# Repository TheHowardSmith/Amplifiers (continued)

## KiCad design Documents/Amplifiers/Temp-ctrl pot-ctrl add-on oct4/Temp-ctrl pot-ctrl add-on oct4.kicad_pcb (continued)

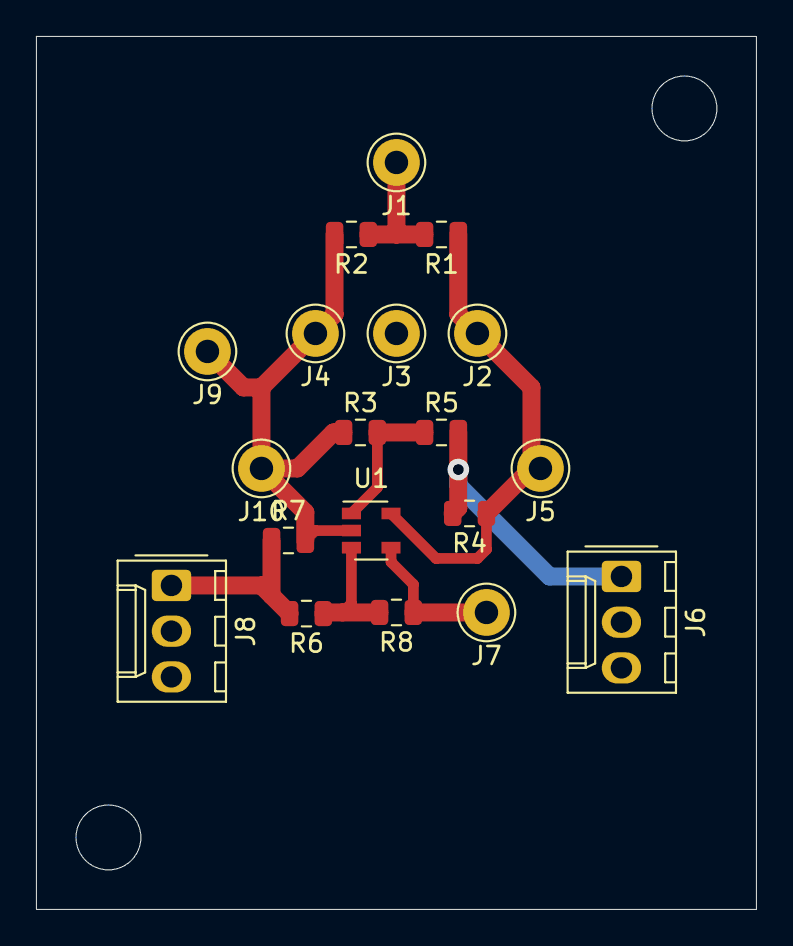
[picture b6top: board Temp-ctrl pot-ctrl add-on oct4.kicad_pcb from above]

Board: 2 copper layers, 40.0 x 48.5 mm, 19 parts (0 on the bottom side), 8 nets.

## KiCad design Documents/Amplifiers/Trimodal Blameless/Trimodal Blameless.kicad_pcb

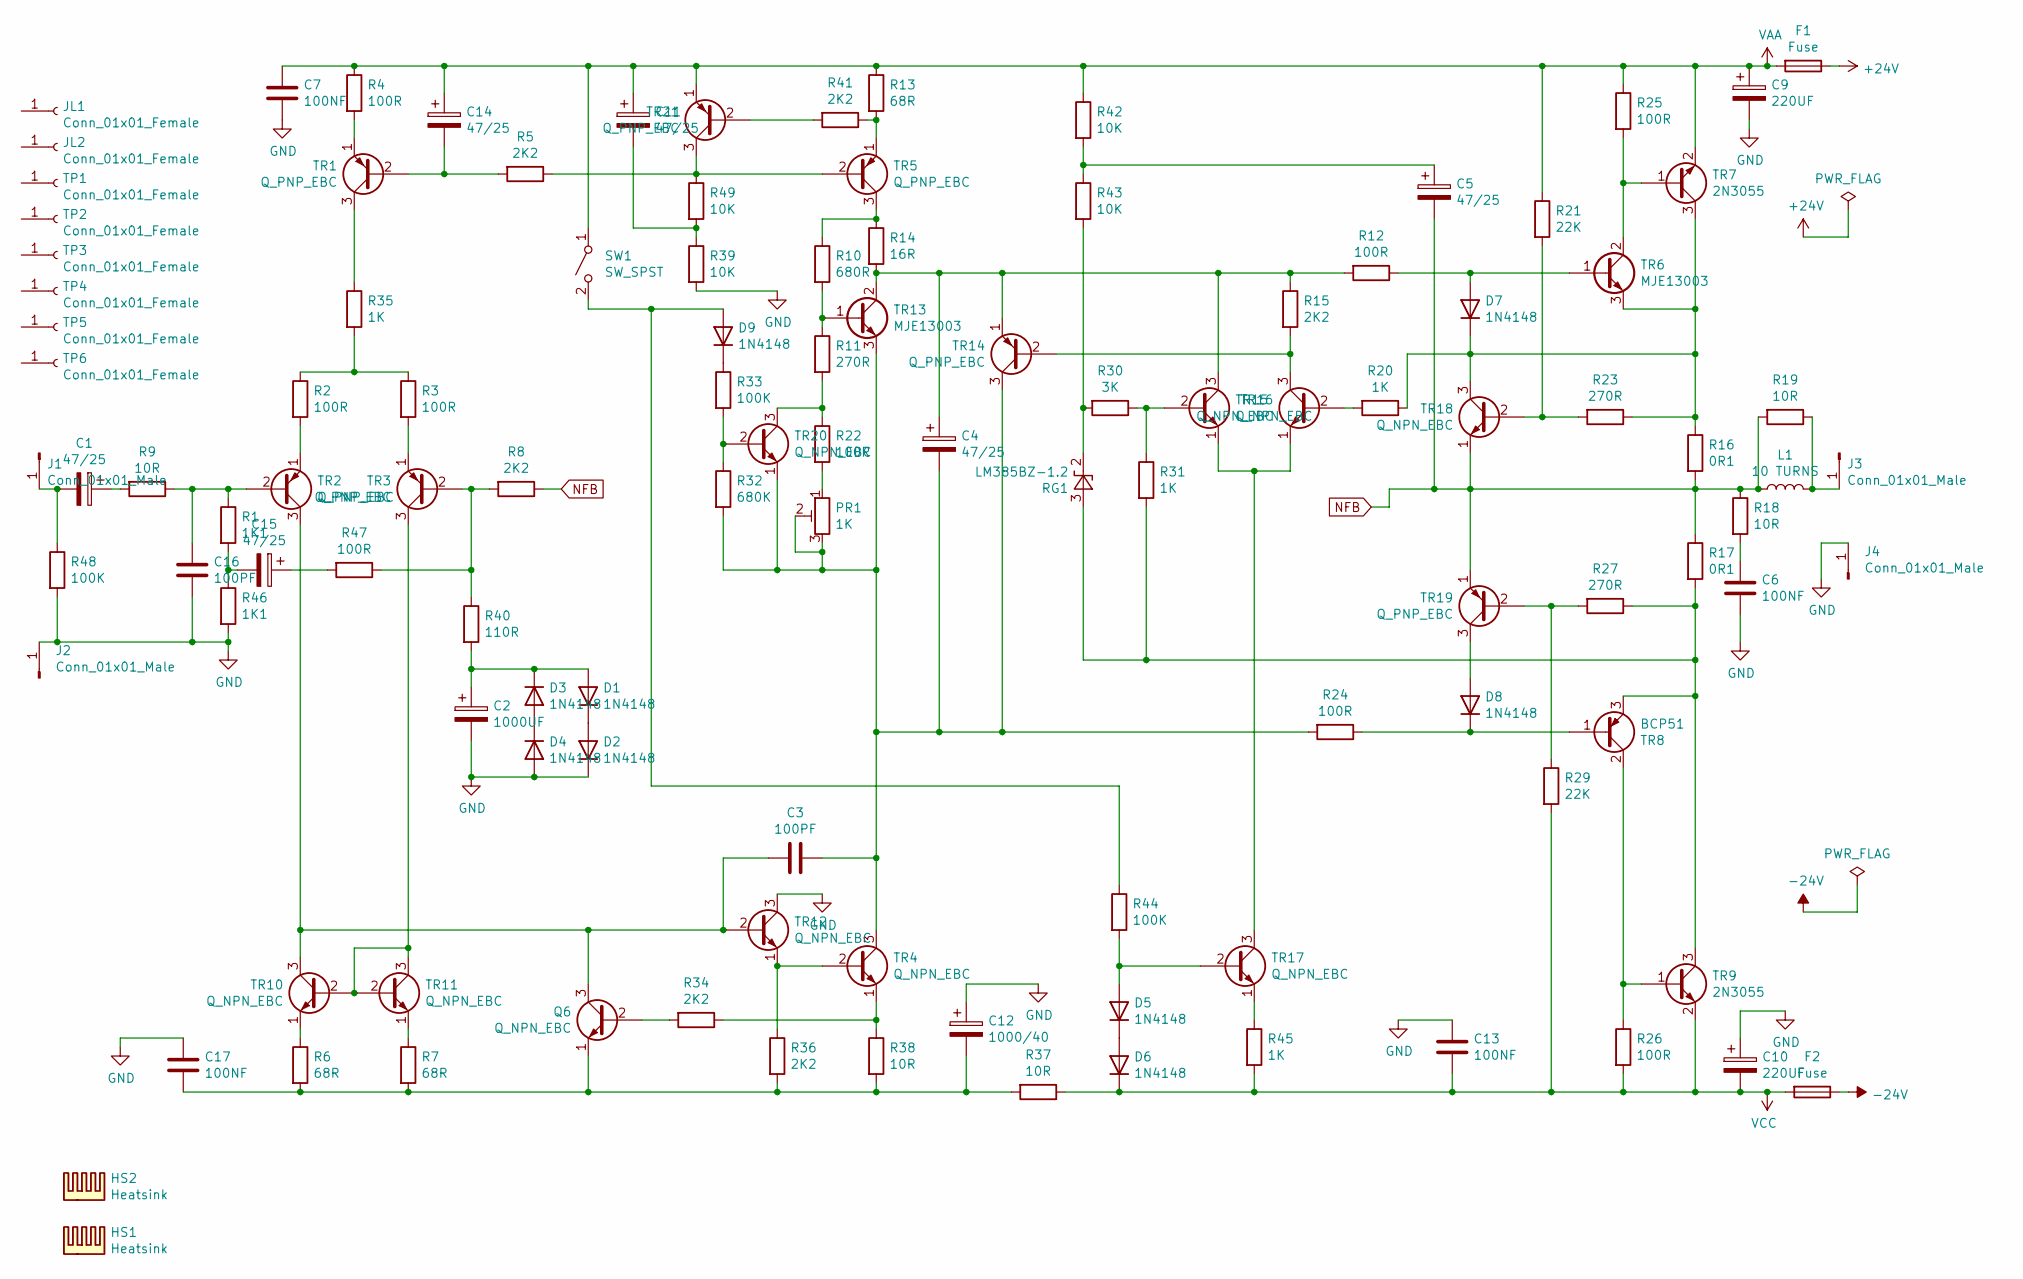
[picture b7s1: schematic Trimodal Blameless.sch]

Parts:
C1, C4, C5, C11, C14, C15: 47/25; CP_Radial_D8.0mm_P5.00mm
C2: 1000UF; CP_Radial_D10.0mm_P5.00mm
C3, C16: 100PF; C_Disc_D4.3mm_W1.9mm_P5.00mm
C6, C7, C13, C17: 100NF; C_Rect_L11.0mm_W3.5mm_P10.00mm_MKT
C9, C10: 220UF; CP_Radial_D10.0mm_P5.00mm
C12: 1000/40; CP_Radial_D12.5mm_P5.00mm
D1, D2, D3, D4, D5, D6, D7, D8, D9: 1N4148; D_DO-41_SOD81_P7.62mm_Horizontal
F1, F2: Fuse; Fuseholder_Cylinder-5x20mm_Stelvio-Kontek_PTF78_Horizontal_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
HS1, HS2: Heatsink; Heatsink_Fischer_SK104-STCB_35x13mm__2xDrill3.5mm_ScrewM3
J1, J2, J3, J4: Conn_01x01_Male; Pin_D1.3mm_L11.0mm
JL1, JL2: Conn_01x01_Female; Pin_D1.3mm_L11.0mm
L1: 10 TURNS; L_Axial_L20.3mm_D12.7mm_P25.40mm_Horizontal_Vishay_IHA-201
PR1: 1K; Potentiometer_ACP_CA9-V10_Vertical
Q6: Q_NPN_EBC; TO-92
R1, R46: 1K1; R_Axial_DIN0207_L6.3mm_D2.5mm_P10.16mm_Horizontal
R2, R3, R4, R12, R22, R24, R25, R26, R47: 100R; R_Axial_DIN0207_L6.3mm_D2.5mm_P10.16mm_Horizontal
R5, R8, R15, R34, R36, R41: 2K2; R_Axial_DIN0207_L6.3mm_D2.5mm_P10.16mm_Horizontal
R6, R7, R13: 68R; R_Axial_DIN0207_L6.3mm_D2.5mm_P10.16mm_Horizontal
R9, R18, R19, R37, R38: 10R; R_Axial_DIN0207_L6.3mm_D2.5mm_P10.16mm_Horizontal
R10: 680R; R_Axial_DIN0207_L6.3mm_D2.5mm_P10.16mm_Horizontal
R11, R23, R27: 270R; R_Axial_DIN0207_L6.3mm_D2.5mm_P10.16mm_Horizontal
R14: 16R; R_Axial_DIN0207_L6.3mm_D2.5mm_P10.16mm_Horizontal
R16, R17: 0R1; R_Axial_DIN0922_L20.0mm_D9.0mm_P30.48mm_Horizontal
R20, R31, R35, R45: 1K; R_Axial_DIN0207_L6.3mm_D2.5mm_P10.16mm_Horizontal
R21, R29: 22K; R_Axial_DIN0207_L6.3mm_D2.5mm_P10.16mm_Horizontal
R30: 3K; R_Axial_DIN0207_L6.3mm_D2.5mm_P10.16mm_Horizontal
R32: 680K; R_Axial_DIN0207_L6.3mm_D2.5mm_P10.16mm_Horizontal
R33, R44, R48: 100K; R_Axial_DIN0207_L6.3mm_D2.5mm_P10.16mm_Horizontal
R39, R42, R43, R49: 10K; R_Axial_DIN0207_L6.3mm_D2.5mm_P10.16mm_Horizontal
R40: 110R; R_Axial_DIN0207_L6.3mm_D2.5mm_P10.16mm_Horizontal
RG1: LM385BZ-1.2; TO-92_Inline
SW1: SW_SPST; SW_NKK_G1xJP
TP1, TP2, TP3, TP4, TP5, TP6: Conn_01x01_Female; Pin_D1.3mm_L11.0mm
TR1, TR2, TR3, TR5, TR14, TR19, TR21: Q_PNP_EBC; TO-92
TR4, TR10, TR11, TR12, TR15, TR16, TR17, TR18, TR20: Q_NPN_EBC; TO-92
TR6, TR13: MJE13003; TO-126-3_Vertical
TR7, TR9: 2N3055; TO-3
TR8: BCP51; TO-126-3_Vertical

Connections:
+24V: F1.1
-24V: F2.1
GND: C2.2, C6.2, C7.2, C9.2, C10.1, C12.1, C13.1, C16.2, C17.1, D2.1 (K), D4.2 (A), J2.1, J4.1, R39.2, R46.2, R48.2, TR12.3 (C)
NFB: C5.2, L1.1, R8.1, R16.2, R17.1, R18.1, R19.2, TR18.1 (E), TR19.1 (E)
unnamed: C1.1, R9.2
unnamed: C1.2, J1.1, R48.1
unnamed: C2.1, D1.2 (A), D3.1 (K), R40.2
unnamed: C3.1, C4.2, PR1.2, PR1.3, R24.2, R32.2, TR4.3 (C), TR13.3 (E), TR14.3 (C), TR20.1 (E)
unnamed: C3.2, Q6.3 (C), TR2.3 (C), TR10.3 (C), TR12.2 (B)
unnamed: C4.1, R12.2, R14.2, R15.1, TR13.2 (C), TR14.1 (E), TR15.3 (C)
unnamed: C5.1, R42.2, R43.1
unnamed: C6.1, R18.2
unnamed: C11.2, R39.1, R49.2
unnamed: C12.2, C17.2, Q6.1 (E), R6.2, R7.2, R36.2, R37.2, R38.2
unnamed: C14.2, R5.2, TR1.2 (B)
unnamed: C15.1, R47.2
unnamed: C15.2, R1.2, R46.1
unnamed: C16.1, R1.1, R9.1, TR2.2 (B)
unnamed: D1.1 (K), D2.2 (A)
unnamed: D3.2 (A), D4.1 (K)
unnamed: D5.1 (K), D6.2 (A)
unnamed: D5.2 (A), R44.2, TR17.2 (B)
unnamed: D7.1 (K), R16.1, R20.1, R23.1, TR6.3 (E), TR7.3 (C), TR18.3 (C)
unnamed: D7.2 (A), R12.1, TR6.1 (B)
unnamed: D8.1 (K), R24.1, TR8.1 (B)
unnamed: D8.2 (A), TR19.3 (C)
unnamed: D9.1 (K), R33.1
unnamed: D9.2 (A), R44.1, SW1.2 (B)
unnamed: J3.1, L1.2, R19.1
unnamed: PR1.1, R22.2
unnamed: Q6.2 (B), R34.2
unnamed: R2.1, R3.1, R35.2
unnamed: R2.2, TR2.1 (E)
unnamed: R3.2, TR3.1 (E)
unnamed: R4.2, TR1.1 (E)
unnamed: R6.1, TR10.1 (E)
unnamed: R7.1, TR11.1 (E)
unnamed: R10.1, R14.1, TR5.3 (C)
unnamed: R10.2, R11.1, TR13.1 (B)
unnamed: R11.2, R22.1, TR20.3 (C)
unnamed: R13.2, R41.1, TR5.1 (E)
unnamed: R15.2, TR14.2 (B), TR16.3 (C)
unnamed: R20.2, TR16.2 (B)
unnamed: R21.2, R23.2, TR18.2 (B)
unnamed: R25.2, TR6.2 (C), TR7.1 (B)
unnamed: R27.2, R29.1, TR19.2 (B)
unnamed: R30.1, R31.1, TR15.2 (B)
unnamed: R30.2, R43.2, RG1.2 (K)
unnamed: R32.1, R33.2, TR20.2 (B)
unnamed: R34.1, R38.1, TR4.1 (E)
unnamed: R35.1, TR1.3 (C)
unnamed: R36.1, TR4.2 (B), TR12.1 (E)
unnamed: R8.2, R40.1, R47.1, TR3.2 (B)
unnamed: R41.2, TR21.2 (B)
unnamed: R45.1, TR17.1 (E)
unnamed: R5.1, R49.1, TR5.2 (B), TR21.3 (C)
unnamed: TR3.3 (C), TR10.2 (B), TR11.2 (B), TR11.3 (C)
unnamed: TR15.1 (E), TR16.1 (E), TR17.3 (C)
VAA: C7.1, C9.1, C11.1, C14.1, F1.2, R4.1, R13.1, R21.1, R25.1, R42.1, SW1.1 (A), TR7.2 (E), TR21.1 (E)
VCC: C10.2, C13.2, D6.1 (K), F2.2, R26.2, R29.2, R37.1, R45.2, TR9.2 (E)

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
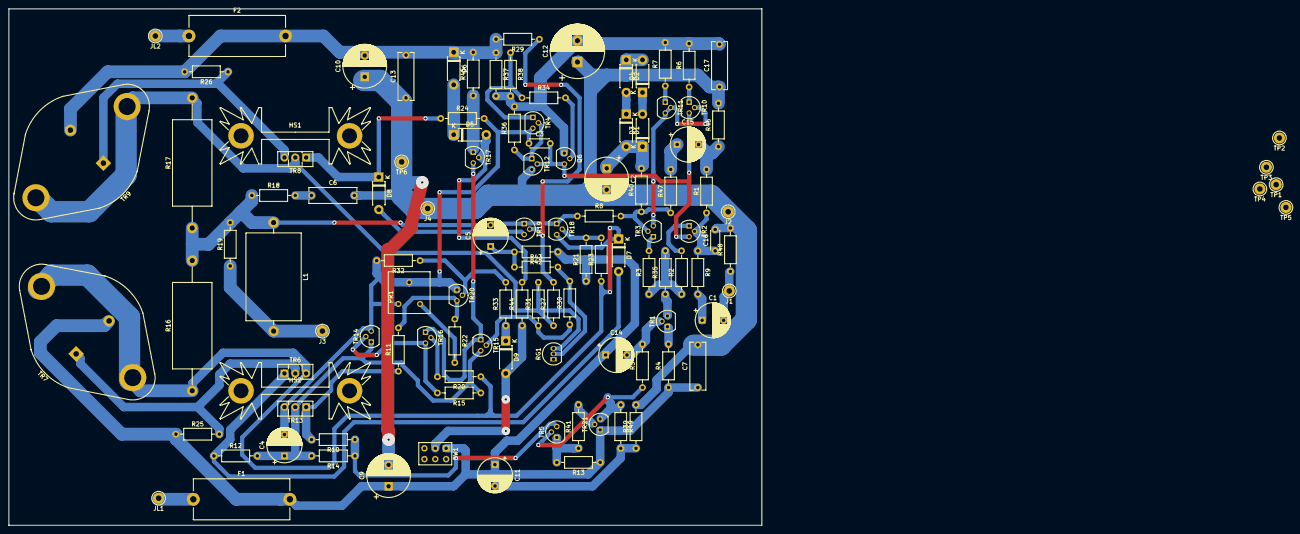
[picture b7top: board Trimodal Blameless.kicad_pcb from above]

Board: 2 copper layers, 176.3 x 120.9 mm, 115 parts (0 on the bottom side), 60 nets.

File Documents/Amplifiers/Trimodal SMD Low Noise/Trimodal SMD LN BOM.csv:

Comment,Designator,Footprint,LCSC
220UF,"C10,C9",Capacitor_SMD:CP_Elec_10x10,C176670
47/25,"C14,C1,C15,C11,C4,C5",Capacitor_SMD:CP_Elec_6.3x5.3,C249976
100PF,"C16,C3",Capacitor_SMD:C_0805_2012Metric,C1790
100NF,"C7,C17,C6,C13",Capacitor_SMD:C_0805_2012Metric,C49678
1N4148,"D3,D4,D1,D2,D9,D6,D5,D7,D8",Diode_SMD:D_SOD-123,C81598
1K1,"R1,R46",Resistor_SMD:R_0805_2012Metric,
680R,R10,Resistor_SMD:R_0805_2012Metric,
270R,"R11,R23,R27",Resistor_SMD:R_0805_2012Metric,
16R,R14,Resistor_SMD:R_0805_2012Metric,
0R1,"R16,R17,R166,R177",Resistor_SMD:R_2512_6332Metric,C78195
22K,"R21,R29",Resistor_SMD:R_0805_2012Metric,
3K,R30,Resistor_SMD:R_0805_2012Metric,
680K,R32,Resistor_SMD:R_0805_2012Metric,
1K,"R35,R45,R31,R20",Resistor_SMD:R_0805_2012Metric,
100R,"R4,R2,R3,R47,R24,R12,R25,R26,R22",Resistor_SMD:R_0805_2012Metric,
110R,R40,Resistor_SMD:R_0805_2012Metric,
100K,"R48,R33,R44",Resistor_SMD:R_0805_2012Metric,
10K,"R49,R39,R42,R43",Resistor_SMD:R_0805_2012Metric,
2K2,"R5,R8,R41,R36,R34,R15",Resistor_SMD:R_0805_2012Metric,
68R,"R6,R7,R13",Resistor_SMD:R_0805_2012Metric,
10R,"R9,R38,R37,R18,R19",Resistor_SMD:R_0805_2012Metric,
LM385M3X-2.5,RG1,Package_TO_SOT_SMD:SOT-23,C83345
SW_SPST,SW1,Package_SO:SOP-4_3.8x4.1mm_P2.54mm,C459807
Q_PNP_EBC,"TR1,TR3,TR2,TR21,TR5,TR14,TR19",Package_TO_SOT_SMD:SOT-89-3,C24278
Q_NPN_EBC,"TR10,TR11,TR20,TR4,TR12,Q6,TR15,TR16,TR18,TR17",Package_TO_SOT_SMD:SOT-89-3,C9634

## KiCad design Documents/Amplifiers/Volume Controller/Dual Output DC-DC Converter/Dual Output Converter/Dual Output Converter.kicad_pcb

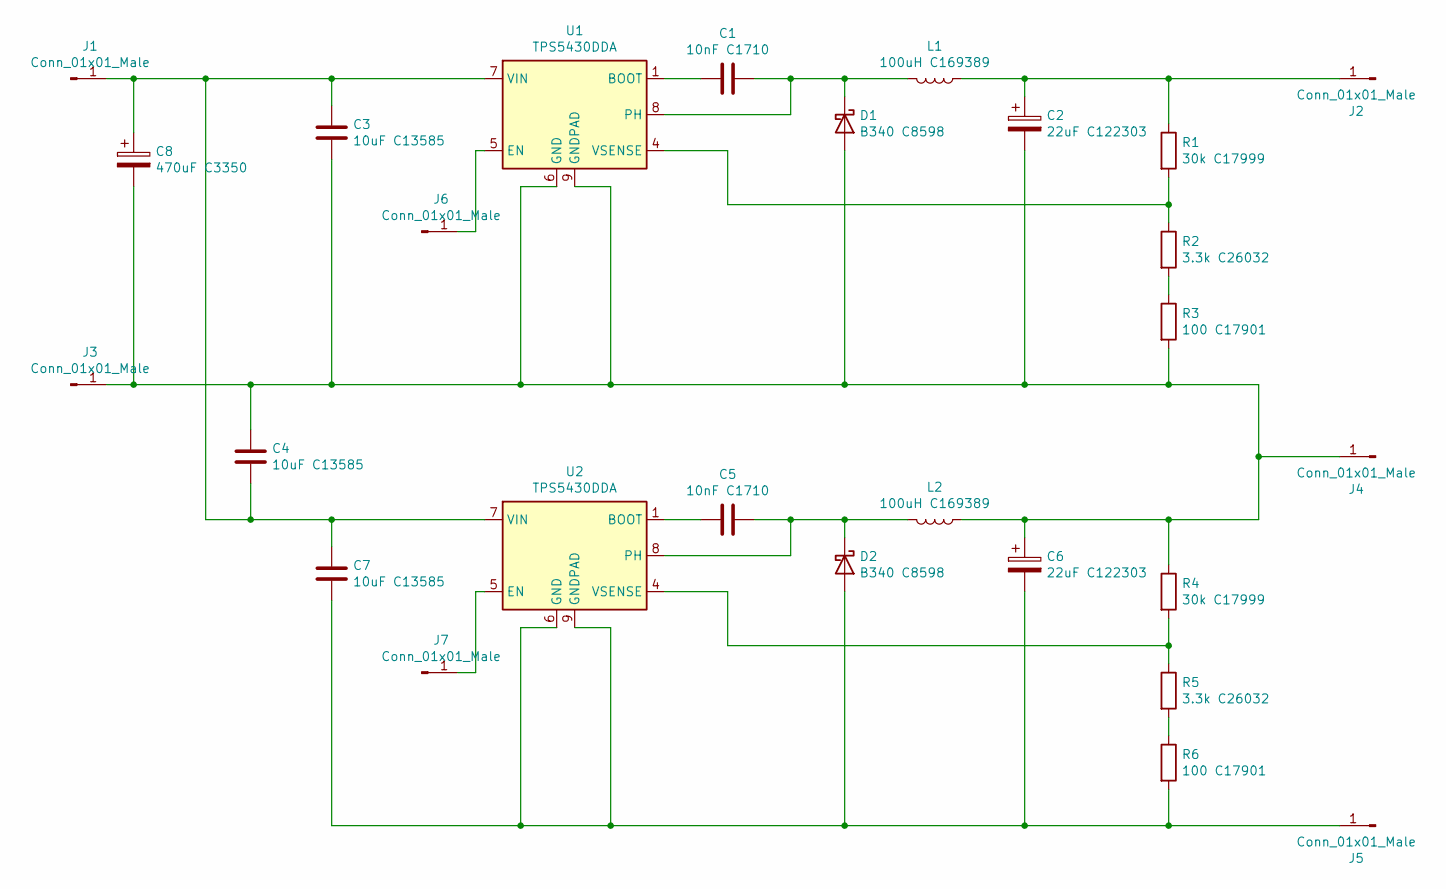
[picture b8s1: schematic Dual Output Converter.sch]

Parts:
C1, C5: 10nF C1710; C_0805_2012Metric
C2, C6: 22uF C122303; CP_EIA-7343-31_Kemet-D
C3, C4, C7: 10uF C13585; C_0805_2012Metric
C8: 470uF C3350; CP_Elec_10x10
D1, D2: B340 C8598; D_SOD-123
J1, J2, J3, J4, J5, J6, J7: Conn_01x01_Male; Pin_D1.3mm_L11.0mm
L1, L2: 100uH C169389; L_12x12mm_H6mm
R1, R4: 30k C17999; R_1206_3216Metric
R2, R5: 3.3k C26032; R_1206_3216Metric
R3, R6: 100 C17901; R_1206_3216Metric
U1, U2: TPS5430DDA; TI_SO-PowerPAD-8_ThermalVias

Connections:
unnamed: C1.1, D1.1 (K), L1.2, U1.8 (PH)
unnamed: C1.2, U1.1 (BOOT)
unnamed: C2.1, J2.1, L1.1, R1.1
unnamed: C2.2, C3.2, C4.1, C6.1, C8.2, D1.2 (A), J3.1, J4.1, L2.1, R3.2, R4.1, U1.6 (GND), U1.9 (GNDPAD)
unnamed: C3.1, C4.2, C7.1, C8.1, J1.1, U1.7 (VIN), U2.7 (VIN)
unnamed: C5.1, D2.1 (K), L2.2, U2.8 (PH)
unnamed: C5.2, U2.1 (BOOT)
unnamed: C6.2, C7.2, D2.2 (A), J5.1, R6.2, U2.6 (GND), U2.9 (GNDPAD)
unnamed: J6.1, U1.5 (EN)
unnamed: J7.1, U2.5 (EN)
unnamed: R1.2, R2.1, U1.4 (VSENSE)
unnamed: R2.2, R3.1
unnamed: R4.2, R5.1, U2.4 (VSENSE)
unnamed: R5.2, R6.1

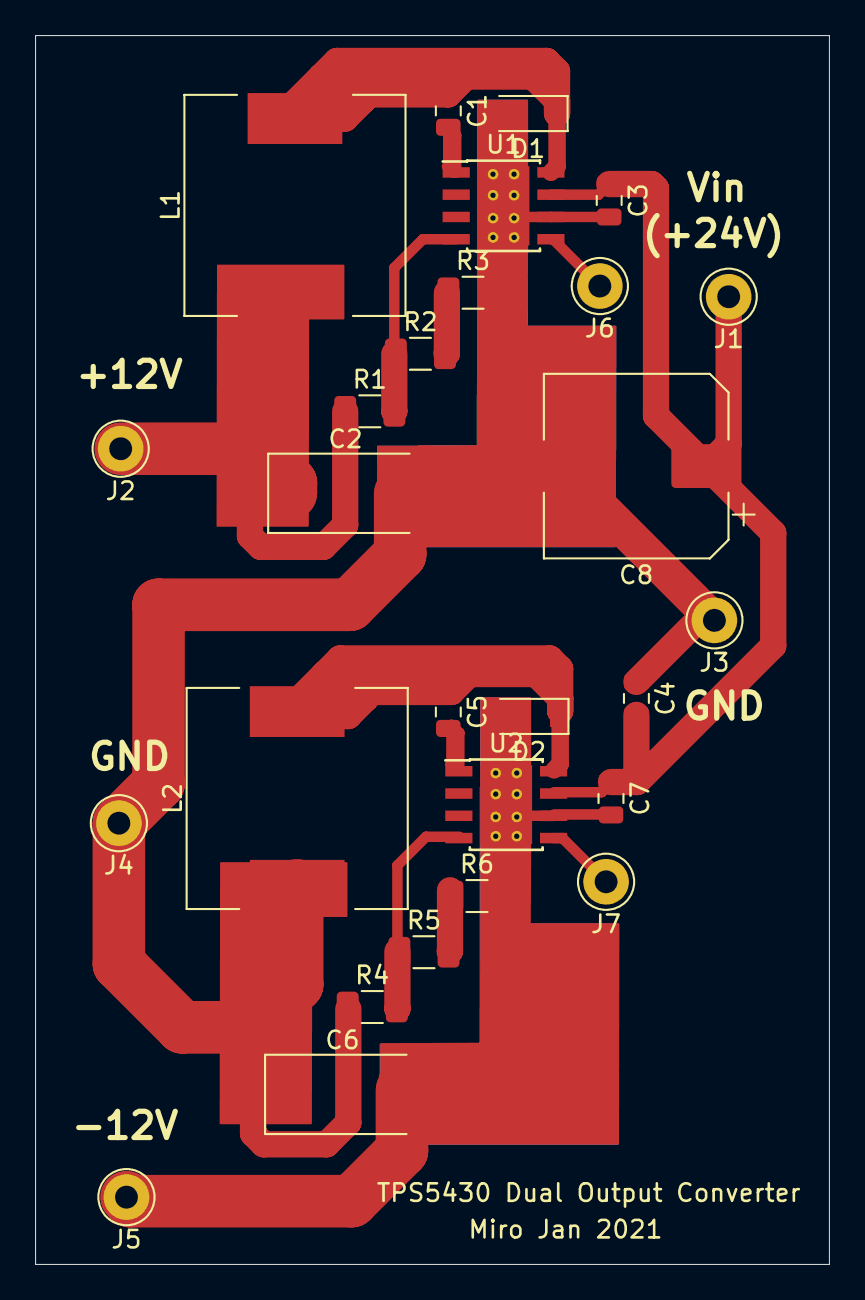
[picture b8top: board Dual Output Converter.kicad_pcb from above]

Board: 2 copper layers, 45.2 x 70.0 mm, 27 parts (0 on the bottom side), 14 nets.

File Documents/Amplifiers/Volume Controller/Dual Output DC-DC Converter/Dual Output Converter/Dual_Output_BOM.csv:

Comment,Designator,Footprint,LCSC
10nF,"C1,C5",Capacitor_SMD:C_0805_2012Metric,C1710
22uF,"C2,C6",Capacitor_Tantalum_SMD:CP_EIA-7343-31_Kemet-D,C122303
10uF,"C3,C7,C4",Capacitor_SMD:C_0805_2012Metric,C13585
470uF,C8,Capacitor_SMD:CP_Elec_10x10,C3350
B340,"D1,D2",Diode_SMD:D_SOD-123,C8598
100uH,"L1,L2",Inductor_SMD:L_12x12mm_H6mm,C169389
30k,"R1,R4",Resistor_SMD:R_1206_3216Metric,C17999
3.3k,"R2,R5",Resistor_SMD:R_1206_3216Metric,C26032
100R,"R3,R6",Resistor_SMD:R_1206_3216Metric,C17901
TPS5430DDA,"U1,U2",Package_SO:TI_SO-PowerPAD-8_ThermalVias,C9864
